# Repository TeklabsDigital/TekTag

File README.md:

# **TekTag Bio™ - The Open Source Biosensor**

Introducing the latest open-source project from Teklabs Digital™, a sophisticated state-of-the-art IoT biosensor for patient monitoring, telehealth, pressure are management in hospitals, cardiac monitoring, fall detection and dementia geofencing. This community project, released under an open source license, showcases our commitment to pushing the boundaries of digital design innovation.

**TekTag Bio™** is a cutting-edge biosensor for telehealth, patient monitoring, fall detection, dementia geofencing, and cardiograms. This repository houses all the necessary files and resources to understand, modify, and contribute to this innovative project.

## **Table of Contents**

- [Features](#features)
- [Biosensor Applications](#biosensor-applications)
- [General Applications](#general-applications)
- [BLE Support and Mesh Technology](#ble-support-and-mesh-technology)
  - [Benefits of BLE Mesh Technology](#benefits-of-ble-mesh-technology)
- [Hardware/Electronics](#hardwareelectronics)
- [Repository Structure](#repository-structure)
- [Images](#images)
- [PCB Size and Assembly](#pcb-size-and-assembly)
- [Why is this project Open Source?](#why-is-this-project-open-source)
- [Supporting This Project](#supporting-this-project)
- [Licenses](#licenses)
- [Contact Us](#contact-us)

## [**Features**](#features)
- Small size - 28mm diameter (1.1 inches)
- All 3D manufacturing files included
- All PCB designs included
- All schematics included
- Audio feedback
- BLE 5.4 - Mesh Networking & All protocols supported by the STM32WB
- Compact integrated design
- Haptic feedback
- Qi charging
- STM32WB ARM MCU
- Touch pad for finger tap and gestures
- Ultra low power
- Visual feedback through two RGB LEDs

## [Biosensor Applications](#biosensor-applications)

Our biosensor provides a plethora of features designed to enhance the quality of life for individuals and improve the capabilities of healthcare providers. It includes:

- Telehealth capabilities
- Patient monitoring
- Pressure area management - bed turn and movement detection
- Cardiac monitoring via Ballistocardiology (BCG)
- Patient Fall detection
- Dementia geo-fence alerting
- Respiratory monitoring
- Sleep pattern monitoring

## [General Applications](#general-applications)

The small size, wireless Bluetooth, hermetically sealed enclosure, and Qi charging features of the sensor make it versatile enough to be used in a wide variety of applications, such as:

- Sports Performance Analysis
- Physical Therapy
- Elderly Care
- Virtual Reality (VR)/ Augmented Reality (AR) Systems
- Gaming
- Industrial Monitoring
- Sleep Studies
- Dance Choreography
- Wildlife Studies
- Security Systems

## [BLE Support and Mesh Technology](#ble-support-and-mesh-technology)

One of the key features of the TekTag Bio™ is its compatibility with the STM32WB ecosystem, which offers support for a variety of Bluetooth Low Energy (BLE) protocols. BLE is a power-efficient version of classic Bluetooth and is designed for short-range communication between devices. 

A particularly exciting protocol within this ecosystem is BLE Mesh technology. BLE Mesh allows for many-to-many communication, creating a network of interconnected devices that can communicate with each other. This is an essential feature when deploying large numbers of TekTag Bio™ devices in a hospital setting.

### [Benefits of BLE Mesh Technology](#benefits-of-ble-mesh-technology)

There are several key benefits of using BLE Mesh technology in a TekTag Bio™ deployment:

1. **Scalability**: BLE Mesh networks can theoretically support up to 32,767 devices, making them highly scalable. This is ideal for large-scale deployments in hospitals, where you might need to monitor many patients simultaneously.
2. **Reliability**: In a mesh network, data can take multiple paths to reach its destination, which increases the network's overall reliability. If one device fails or is disconnected, the network can automatically reconfigure itself to ensure data still reaches its destination.
3. **Range**: While individual BLE devices have a limited range, a mesh network can extend that range significantly. Each device in the network can act as a relay, passing messages from one device to another. This allows data to travel large distances across the network, making it possible to cover an entire hospital.
4. **Power Efficiency**: Despite their capabilities, BLE Mesh networks are highly power efficient. This is crucial for TekTag Bio™ devices, which need to operate for extended periods without recharging.

## [Hardware/Electronics](#hardwareelectronics)

Our biosensor utilizes a range of high-performance components to achieve its functionality:

- **STM32WB55VG:** This is a BLE 5.3 dual-core, multi-protocol 2.4 GHz radio and ultra-low-power MCU system on chip. Supporting mesh networking, the STM32WB is the brain of our sensor and responsible for signal processing and wireless communication.

- **MLPF-WB55-01E3:** This is an integrated filter module for STM32WB55, by ST. It increases board space through reduced PCB component count.

- **BQ51052BYFP:** This is a high-efficiency, Qi-compliant wireless power receiver. It enables our sensor to be charged wirelessly.

- **TLV75533PDRV:** This is a low-dropout (LDO) regulator with high power-supply rejection ratio (PSRR). It helps to provide stable power supply for our sensor.

- **KTD2052:** This is an LED driver used for status indication in our sensor.

- **LSM6DSV16XTR:** This is a system-in-package featuring a 3D digital accelerometer and a 3D digital gyroscope. It enables our sensor to detect and log movements.

## [Repository Structure](#repository-structure)

This repository is organized into several key sections:

- **Electronics:** Schematics, PCB updates and files related to the electronic components of the TekTag Bio™ biosensor.
- **Firmware/stm32:** The initial commit of the firmware for the STM32 microcontroller used in the device.
- **Mechanical:** Files related to the mechanical aspects of the biosensor, including design and assembly instructions.

## [Images](#images)

Below are some images related to the project:

### PCB Front - 6 Layers
Having a six-layer PCB with tented vias under a BGA (Ball Grid Array) is important for our product's compact size, signal integrity, thermal management, and reliability. The extra layers allow for denser routing, reducing PCB size. Tented vias prevent solder draw into vias, preventing assembly problems under tight constraints.

### PCB Front 3D

### PCB Back 3D

### TekTag Bio™ Sensor with Silicon Holder

### TekTag Bio™ Sensor Without Silicone Holder

## [PCB Size and Assembly](#pcb-size-and-assembly)

The TekTag Bio™ is designed with a compact and highly-integrated PCB (Printed Circuit Board). Given its small size, specialized tools and expertise are required for the assembly process. This could pose a challenge for individual builders, especially those without access to such resources.

Understanding this, if there is enough interest from the community, we are prepared to step in and help. We plan to manufacture and assemble the boards for everyone at minimal cost. This not only ensures the quality and consistency of the boards but also makes the TekTag Bio™ more accessible to everyone interested in using or contributing to it.

## [Why is this project Open Source?](#why-is-this-project-open-source)

TekTag Bio™ is a project rooted in the belief that quality healthcare should be accessible to everyone, regardless of where they are in the world. By open sourcing this project, we are aiming to democratize access to technology that has the potential to significantly improve patient outcomes, particularly in developing countries where resources may be limited. 

There are several reasons why we believe an open source approach is best for this project:

1. **Community Collaboration**: Open source projects foster a unique sense of collaboration and community. People from all around the world can contribute to the project, each bringing their unique perspectives and skills to the table. This diversity can drive innovation and improve the product in ways that wouldn't be possible in a closed source project.

2. **Accelerated Development**: With more eyes on the project, issues can be identified and resolved more quickly. This can speed up the development process and result in a better final product.

3. **Transparency**: Open source projects are transparent. Anyone can look at the code and understand exactly how the product works. This transparency can build trust and make it easier for people to adopt the technology.

4. **Accessibility**: Perhaps the most important reason is that open source projects are accessible to everyone. Anyone, anywhere, can use and modify the product for their own needs. This is particularly important for healthcare technology, which has the potential to save lives and improve quality of life for millions of people.

5. **Non-profit Motivation**: As a non-profit initiative, our primary goal is to support health outcomes worldwide. Our focus is on creating a product that can have a real impact on the world, not on generating profit.

6. **Education**: Open sourcing this project also provides a valuable learning resource for students and professionals interested in biosensor technology. They can learn from and build upon the work that's already been done, accelerating their own learning and development.

By open sourcing TekTag Bio™, we hope to create a product that's not only effective, but also widely accessible and continually improving. This is our contribution to supporting healthcare in both developing countries and in first world hospitals where critical care is needed. We invite you to join us in this endeavor, whether it's by using TekTag Bio™, contributing to its development, or simply learning from the project.

## [Supporting This Project](#supporting-this-project)

TekTag Bio™ is a community-driven project, and we welcome contributions from everyone, regardless of their background or experience level. There are several ways you can support this project:

1. **Contributing Code**: If you have experience in UX/UI for the web application, Node.js for backend development, Express.js for the frontend, or STM32WB firmware engineering, your skills are particularly valuable. You can contribute directly to the codebase, helping us improve and expand the functionality of TekTag Bio™.

2. **Testing and Reporting Issues**: Even if you're not a developer, you can still contribute by testing the TekTag Bio™ and reporting any issues or bugs you find. This helps us ensure that the TekTag Bio™ is as reliable and effective as possible.

3. **Spreading the Word**: Help us grow the TekTag Bio™ community by sharing the project with others. The more people who know about TekTag Bio™, the more we can achieve.

4. **Donations**: As a not-for-profit project, we rely on donations to fund our work. If you're able to, consider making a donation to support the development of TekTag Bio™.

5. **Partnerships**: We are open to partnerships with organizations that align with our mission of improving healthcare outcomes worldwide. If you represent such an organization, please get in touch.

## [Licenses](#licenses)
Project source code, hardware designs and 3d enclosure designs are open source and licensed under the terms of the attached license, with attribution to TekLabs Digital Pty Ltd, Australia

## [Contact Us](#contact-us)
If you're interested in contributing to the TekTag Bio™ project, please contact us through our website at [https://teklabsdigital.com/contact/](https://teklabsdigital.com/contact/). We look forward to working with you to make TekTag Bio™ the best it can be!

Remember, every contribution, no matter how small, helps us move closer to our goal of improving healthcare outcomes around the world. Thank you for your support!

About TekLabs Digital Pty Ltd, Australia - Creating exceptional IoT products and advanced technologies to improve our quality of life 🌟IoT product research, innovation and design✨Let's get started!
web www.teklabsdigital.com
linkedin https://www.linkedin.com/in/trevorattemadigital/
Contact us about your design today.

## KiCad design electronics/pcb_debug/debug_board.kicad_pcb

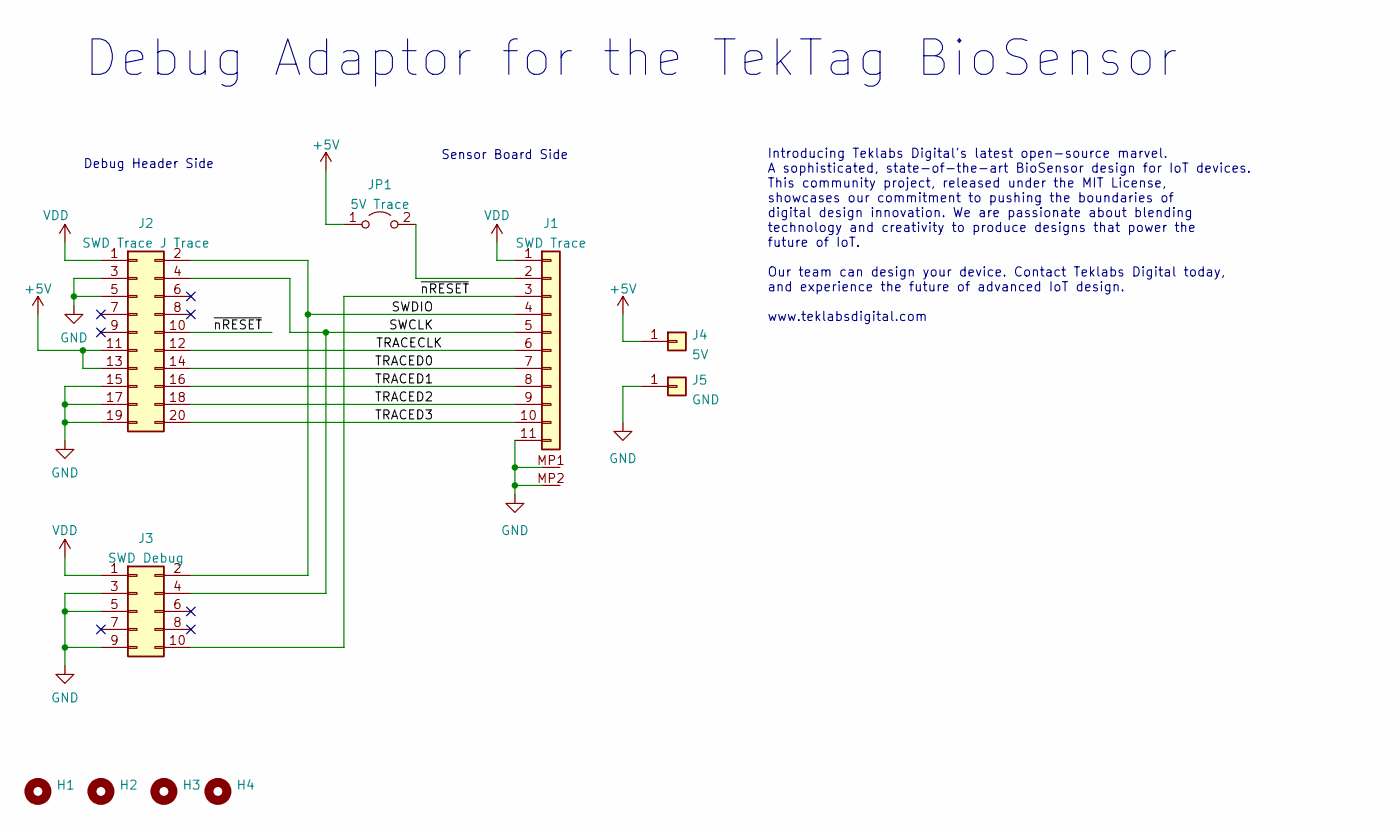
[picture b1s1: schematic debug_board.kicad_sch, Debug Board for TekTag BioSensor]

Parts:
H1, H2, H3, H4: MountingHole; MountingHole_3.7mm_Pad_TopBottom
J1: SWD Trace; Molex 5035661102; Digikey 900-5035661102CT-ND
J2: SWD Trace J Trace; PinHeader_2x10_P1.27mm_Vertical; Digikey 2057-HPH2-A-20-UA-ND
J3: SWD Debug; PinHeader_2x05_P1.27mm_Vertical
J4: 5V; PinHeader_1x01_P2.54mm_Vertical
J5: GND; PinHeader_1x01_P2.54mm_Vertical
JP1: 5V Trace; PinHeader_1x02_P2.54mm_Vertical

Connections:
+5V: J2.11, J2.13, J4.1, JP1.1 (A)
/SWCLK: J1.5, J2.4, J3.4
/SWDIO: J1.4, J2.2, J3.2
/TRACECLK: J1.6, J2.12
/TRACED0: J1.7, J2.14
/TRACED1: J1.8, J2.16
/TRACED2: J1.9, J2.18
/TRACED3: J1.10, J2.20
/~nRESET: J1.3, J2.10, J3.10
GND: J1.11, J1.MP1, J1.MP2, J2.3, J2.5, J2.15, J2.17, J2.19, J3.3, J3.5, J3.9, J5.1
unnamed: J1.2, JP1.2 (B)
VDD: J1.1, J2.1, J3.1

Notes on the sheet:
Sensor Board Side
Debug Adaptor for the TekTag BioSensor
Debug Header Side
Introducing Teklabs Digital's latest open-source marvel. A sophisticated, state-of-the-art BioSensor design for IoT devices. This community project, released under the MIT License, showcases our commitment to pushing the boundaries of digital design innovation. We are passionate about blending tech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

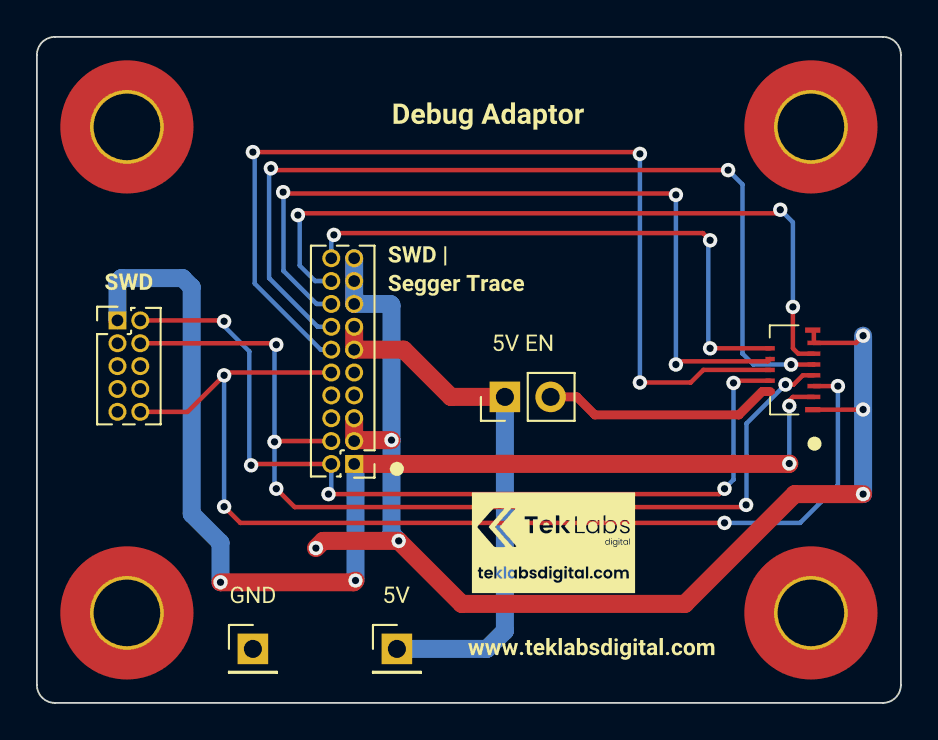
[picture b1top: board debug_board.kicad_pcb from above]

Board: 2 copper layers, 48.0 x 37.0 mm, 17 parts (0 on the bottom side), 12 nets.

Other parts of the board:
kibuzzard-64C06F13: G***; kibuzzard-64C06F13
kibuzzard-64C06F53: G***; kibuzzard-64C06F53
kibuzzard-64C082C5: G***; kibuzzard-64C082C5
kibuzzard-64C0828D: G***; kibuzzard-64C0828D
kibuzzard-64C06064: G***; kibuzzard-64C06064
kibuzzard-64C08352: G***; kibuzzard-64C08352
kibuzzard-64757A2A: G***; kibuzzard-64757A2A

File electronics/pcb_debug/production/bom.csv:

Designator,Footprint,Quantity,Value,LCSC Part #
J1,Molex 5035661102,1,SWD Trace,
J2,PinHeader_2x10_P1.27mm_Vertical,1,SWD Trace J Trace,
J3,PinHeader_2x05_P1.27mm_Vertical,1,SWD Debug,
J4,PinHeader_1x01_P2.54mm_Vertical,1,5V,
J5,PinHeader_1x01_P2.54mm_Vertical,1,GND,
JP1,PinHeader_1x02_P2.54mm_Vertical,1,5V Trace,

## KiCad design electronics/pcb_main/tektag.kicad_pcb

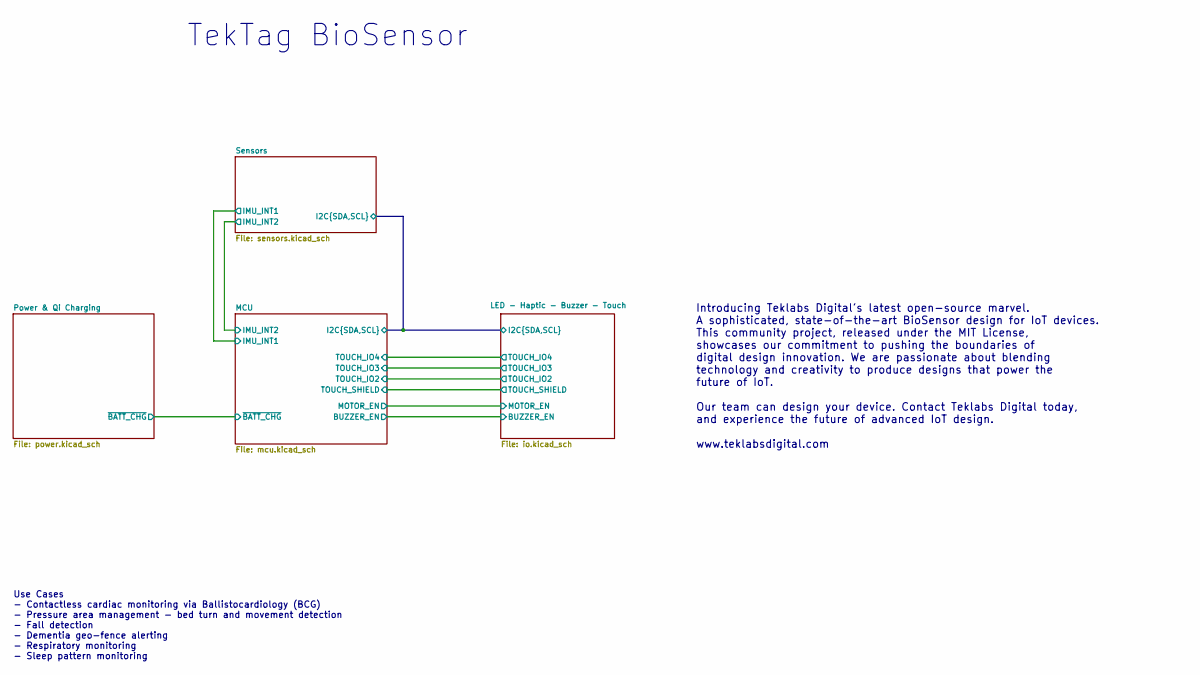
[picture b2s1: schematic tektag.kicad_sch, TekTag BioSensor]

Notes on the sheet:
Introducing Teklabs Digital's latest open-source marvel. A sophisticated, state-of-the-art BioSensor design for IoT devices. This community project, released under the MIT License, showcases our commitment to pushing the boundaries of digital design innovation. We are passionate about blending tech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
Use Cases - Contactless cardiac monitoring via Ballistocardiology (BCG) - Pressure area management - bed turn and movement detection - Fall detection - Dementia geo-fence alerting - Respiratory monitoring - Sleep pattern monitoring
TekTag BioSensor

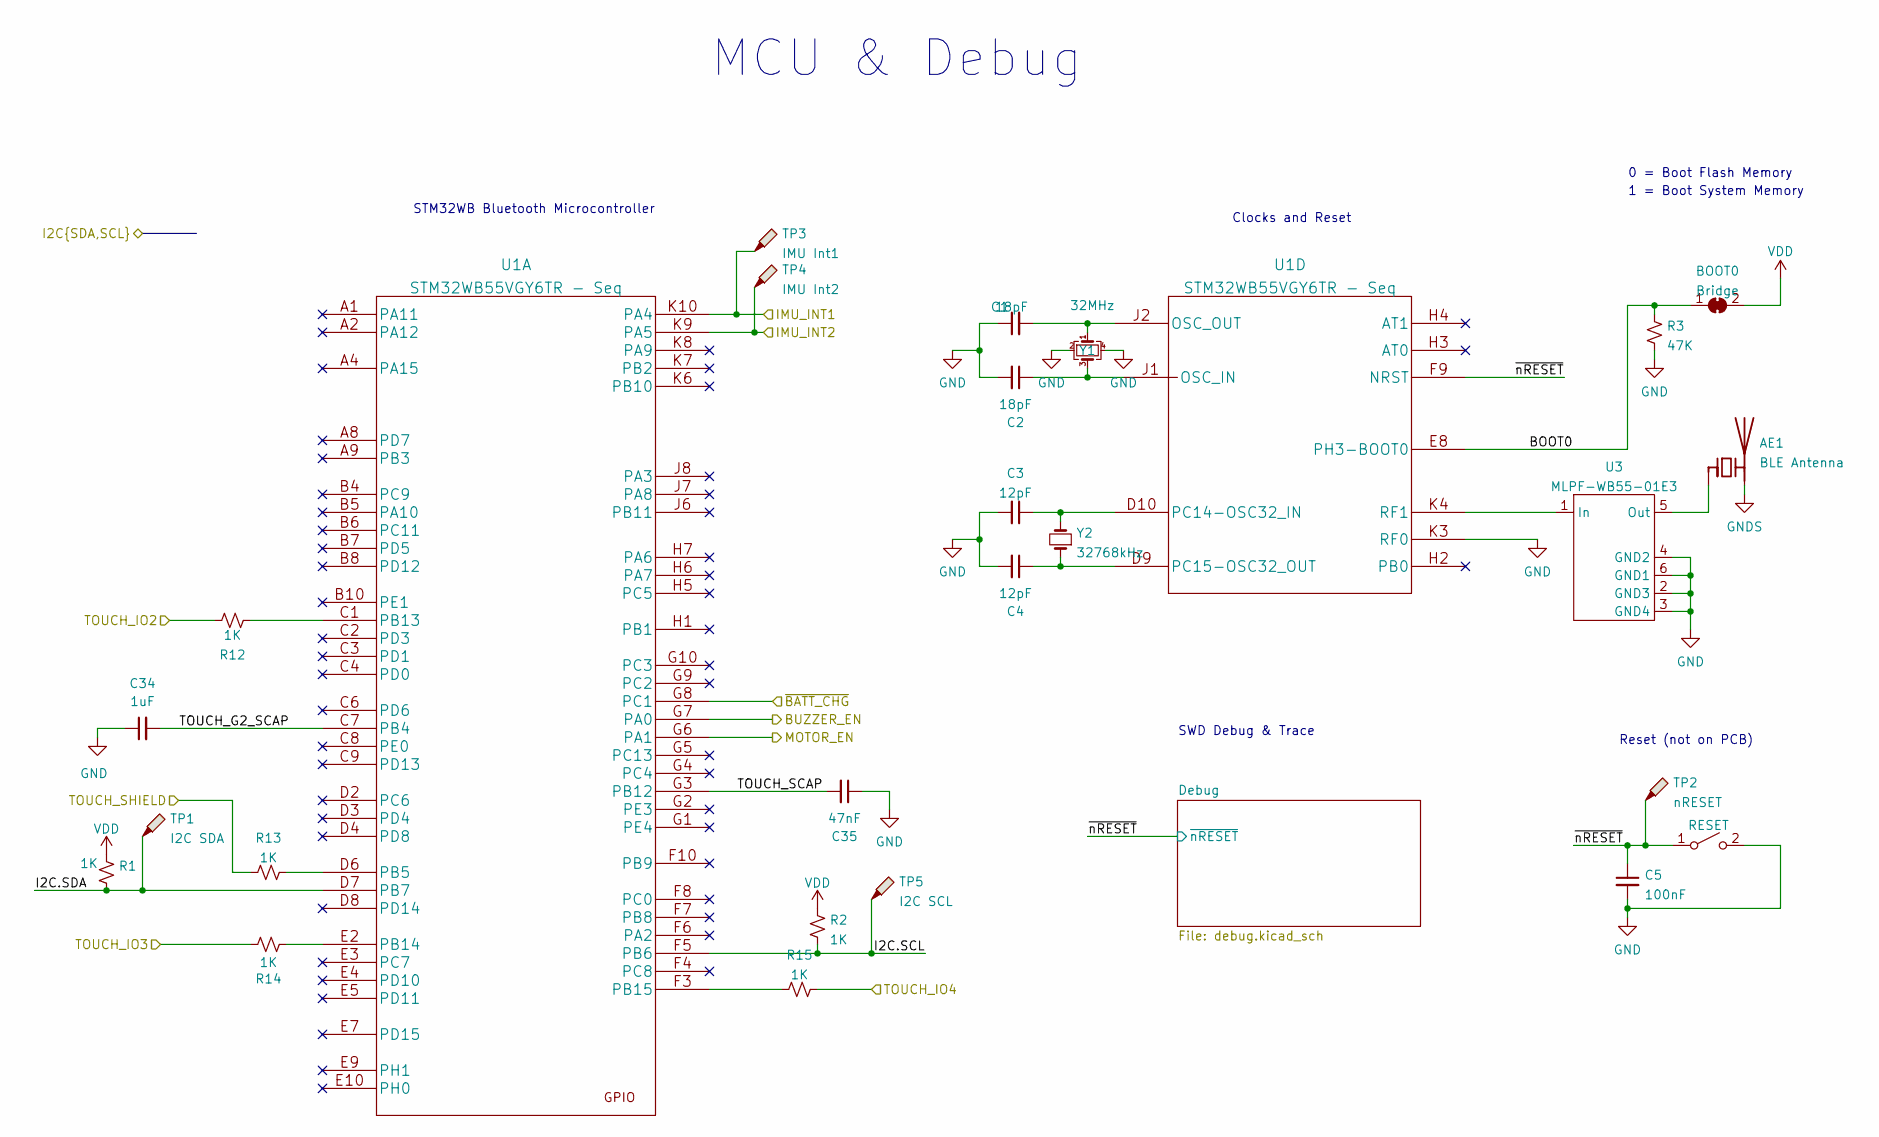
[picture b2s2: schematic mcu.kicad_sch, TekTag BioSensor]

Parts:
AE1: BLE Antenna
BOOT0: Bridge
C1, C2: 18pF; Digikey GCM1555C1H180JA16D
C3, C4: 12pF; Digikey GCM1555C1H120JA16J
C5: 100nF; Digikey GRT155R71H104KE01D
C34: 1uF; Digikey EMK105BJ105KV-F
C35: 47nF; Digikey GRM155R71H473ME14D
R1, R2, R12, R13, R14, R15: 1K; Digikey 1292-WR04X1001FTLCT-ND
R3: 47K; Digikey 311-47.0KLRCT-ND
SW1: RESET; Digikey B3U-1100P
TP1: I2C SDA
TP2: nRESET
TP3: IMU Int1
TP4: IMU Int2
TP5: I2C SCL
U1: STM32WB55VGY6TR - Seq
U3: MLPF-WB55-01E3; Digikey 497-19088-2-ND
Y1: 32MHz; Digikey 1923-830107820709CT-ND
Y2: 32768kHz; Digikey 2195-CM9V-T1A-32.768KHZ-7PF-100PPM-TA-Q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

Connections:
/LED - Haptic - Buzzer - Touch/BUZZER_EN: U1.G7 (PA0); also elsewhere on the board
/LED - Haptic - Buzzer - Touch/I2C.SCL: R2.2, TP5.1, U1.F5 (PB6); also elsewhere on the board
/LED - Haptic - Buzzer - Touch/I2C.SDA: R1.2, TP1.1, U1.D7 (PB7); also elsewhere on the board
/LED - Haptic - Buzzer - Touch/MOTOR_EN: U1.G6 (PA1); also elsewhere on the board
/LED - Haptic - Buzzer - Touch/TOUCH_IO2: R12.2; also elsewhere on the board
/LED - Haptic - Buzzer - Touch/TOUCH_IO3: R14.2; also elsewhere on the board
/LED - Haptic - Buzzer - Touch/TOUCH_IO4: R15.2; also elsewhere on the board
/LED - Haptic - Buzzer - Touch/TOUCH_SHIELD: R13.2; also elsewhere on the board
/MCU/BOOT0: BOOT0.1 (A), R3.1, U1.E8 (PH3-BOOT0)
/MCU/IMU_INT1: TP3.1, U1.K10 (PA4); also elsewhere on the board
/MCU/IMU_INT2: TP4.1, U1.K9 (PA5); also elsewhere on the board
/MCU/TOUCH_G2_SCAP: C34.2, U1.C7 (PB4)
/MCU/TOUCH_SCAP: C35.2, U1.G3 (PB12)
/MCU/~BATT_CHG: U1.G8 (PC1); also elsewhere on the board
/MCU/~nRESET: C5.1, SW1.1 (A), TP2.1, U1.F9 (NRST); also elsewhere on the board
GND: C1.1, C2.2, C3.2, C4.2, C5.2, C34.1, C35.1, R3.2, SW1.2 (B), U1.K3 (RF0), U3.2 (GND3), U3.3 (GND4), U3.4 (GND2), U3.6 (GND1), Y1.2, Y1.4; also elsewhere on the board
GNDS: AE1.2 (PCB_Trace)
unnamed: AE1.1 (FEED), U3.5 (Out)
unnamed: C1.2, U1.J2 (OSC_OUT), Y1.1
unnamed: C2.1, U1.J1 (OSC_IN), Y1.3
unnamed: C3.1, U1.D10 (PC14-OSC32_IN), Y2.2
unnamed: C4.1, U1.D9 (PC15-OSC32_OUT), Y2.1
unnamed: R12.1, U1.C1 (PB13)
unnamed: R13.1, U1.D6 (PB5)
unnamed: R14.1, U1.E2 (PB14)
unnamed: R15.1, U1.F3 (PB15)
unnamed: U1.K4 (RF1), U3.1 (In)
VDD: BOOT0.2 (B), R1.1, R2.1; also elsewhere on the board

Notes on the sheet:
0 = Boot Flash Memory
1 = Boot System Memory
Reset (not on PCB)
MCU & Debug
SWD Debug & Trace
Clocks and Reset
STM32WB Bluetooth Microcontroller

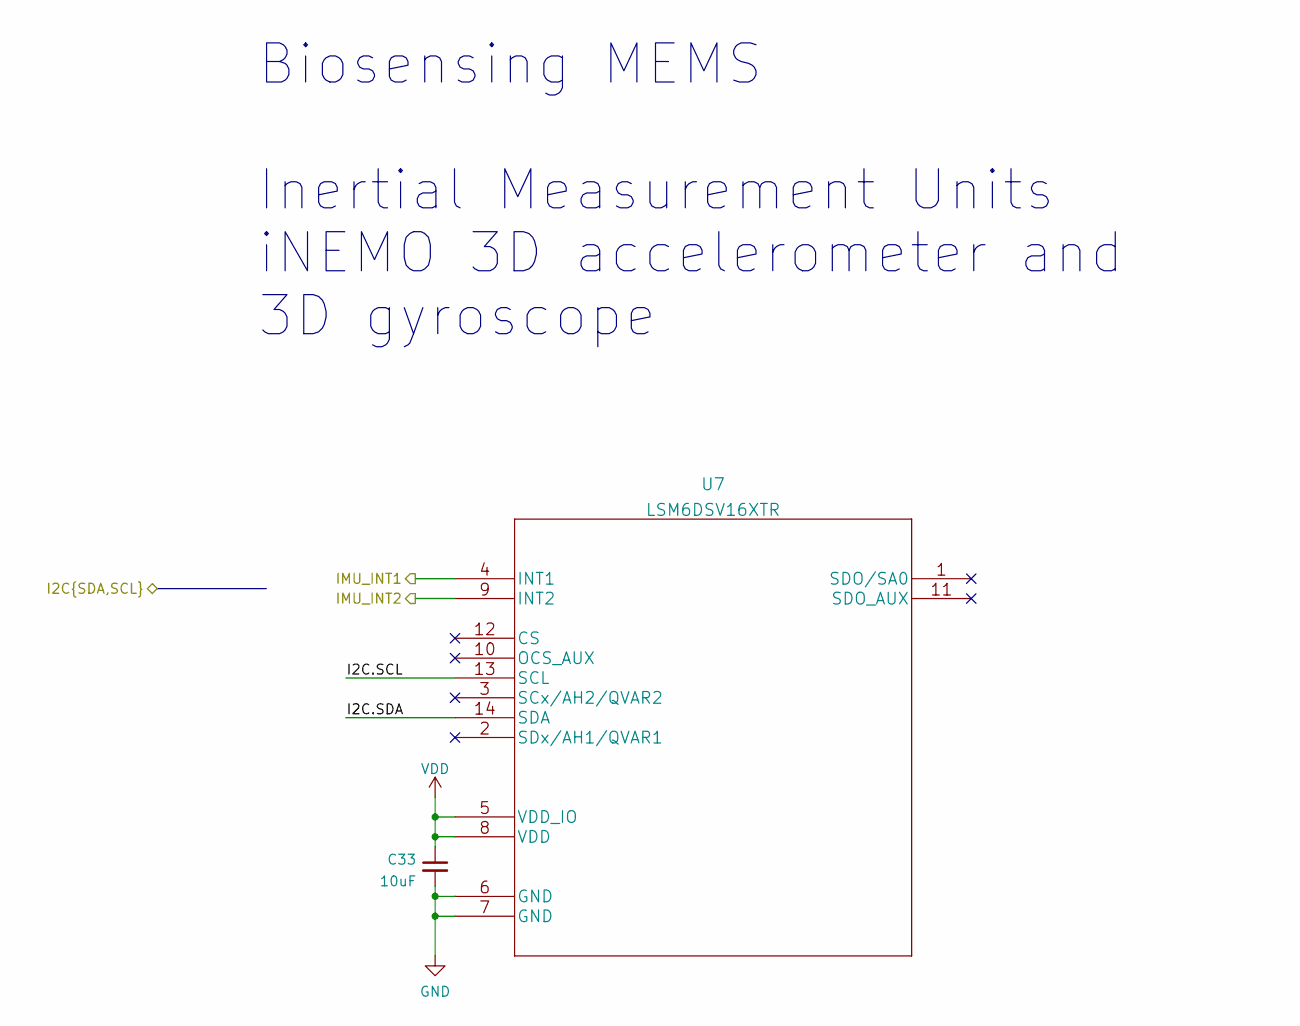
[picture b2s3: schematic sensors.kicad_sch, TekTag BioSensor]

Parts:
C33: 10uF; Digikey GRM188R6YA106MA73D
U7: LSM6DSV16XTR

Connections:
/LED - Haptic - Buzzer - Touch/I2C.SCL: U7.13 (SCL); also elsewhere on the board
/LED - Haptic - Buzzer - Touch/I2C.SDA: U7.14 (SDA); also elsewhere on the board
/MCU/IMU_INT1: U7.4 (INT1); also elsewhere on the board
/MCU/IMU_INT2: U7.9 (INT2); also elsewhere on the board
GND: C33.2, U7.6 (GND), U7.7 (GND); also elsewhere on the board
VDD: C33.1, U7.5 (VDD_IO), U7.8 (VDD); also elsewhere on the board

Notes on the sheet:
Biosensing MEMS Inertial Measurement Units iNEMO 3D accelerometer and 3D gyroscope

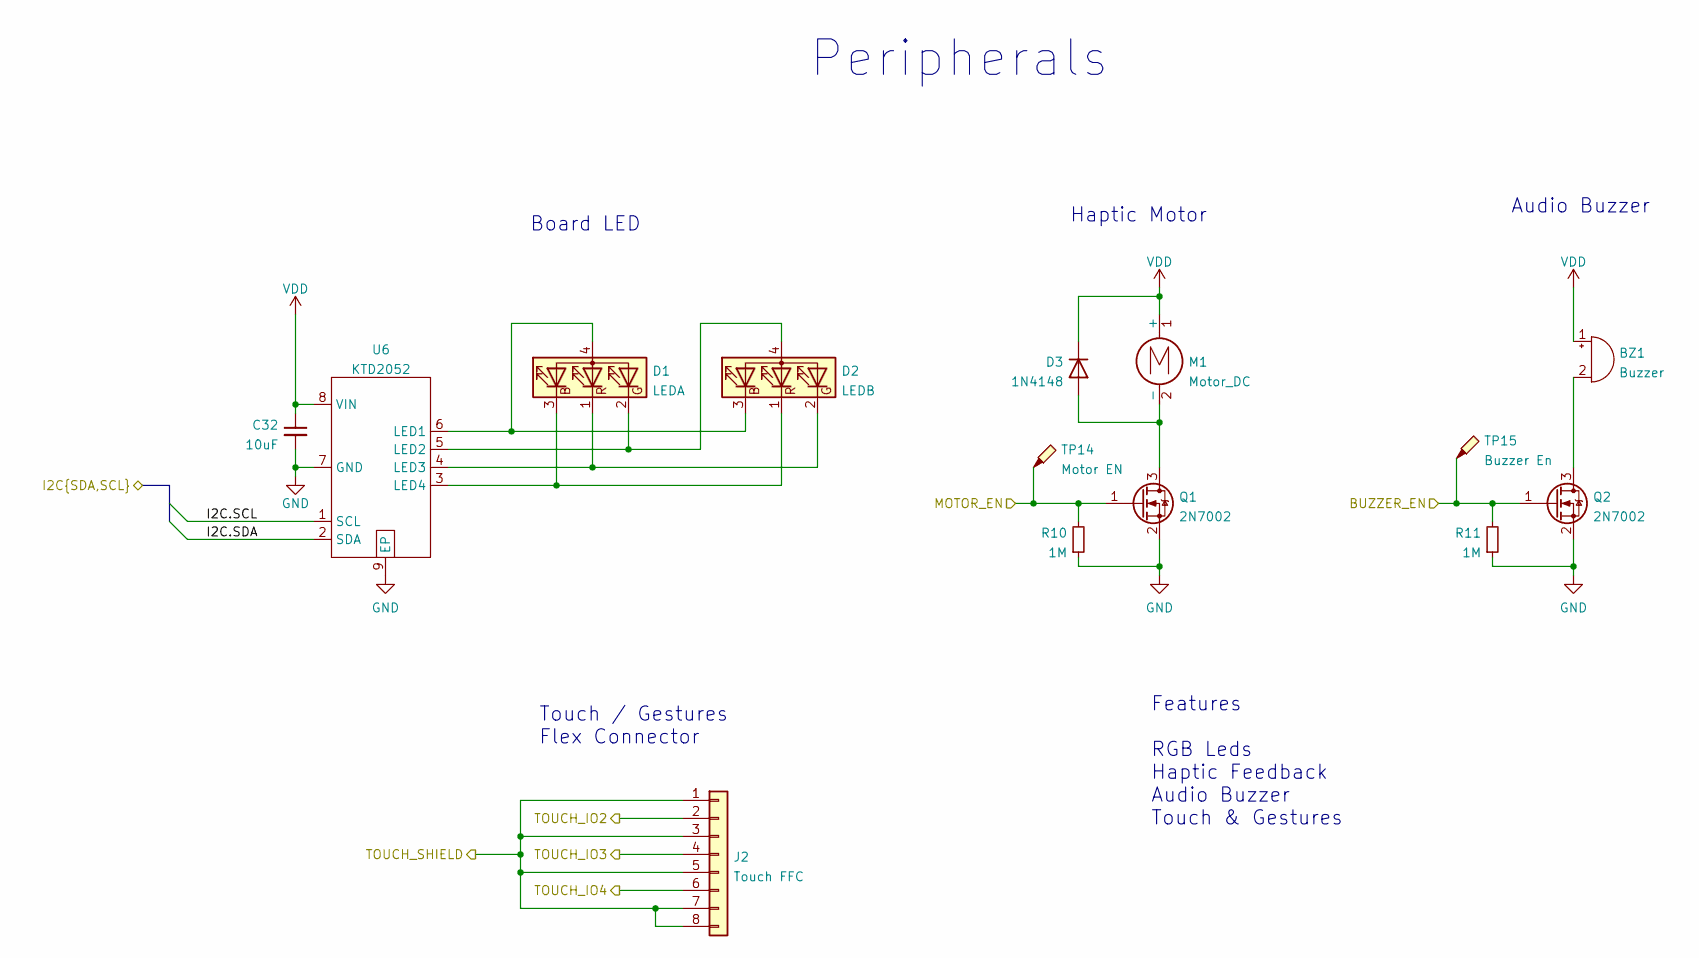
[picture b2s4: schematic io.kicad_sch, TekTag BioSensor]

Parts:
BZ1: Buzzer
C32: 10uF; Digikey GRM188R6YA106MA73D
D1: LEDA; Digikey LTST-C19HE1WT
D2: LEDB; Digikey LTST-C19HE1WT
D3: 1N4148; Digikey 1N4148WL2-TP
J2: Touch FFC
M1: Motor_DC; Digikey 1670-VZ43FM1B8230001LCT-ND
Q1, Q2: 2N7002; Digikey 2N7002KL3A-TP
R10, R11: 1M; Digikey 311-1.00MLRCT-ND
TP14: Motor EN
TP15: Buzzer En
U6: KTD2052

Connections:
/LED - Haptic - Buzzer - Touch/BUZZER_EN: Q2.1 (G), R11.2, TP15.1; also elsewhere on the board
/LED - Haptic - Buzzer - Touch/I2C.SCL: U6.1 (SCL); also elsewhere on the board
/LED - Haptic - Buzzer - Touch/I2C.SDA: U6.2 (SDA); also elsewhere on the board
/LED - Haptic - Buzzer - Touch/MOTOR_EN: Q1.1 (G), R10.2, TP14.1; also elsewhere on the board
/LED - Haptic - Buzzer - Touch/TOUCH_IO2: J2.2; also elsewhere on the board
/LED - Haptic - Buzzer - Touch/TOUCH_IO3: J2.4; also elsewhere on the board
/LED - Haptic - Buzzer - Touch/TOUCH_IO4: J2.6; also elsewhere on the board
/LED - Haptic - Buzzer - Touch/TOUCH_SHIELD: J2.1, J2.3, J2.5, J2.7, J2.8; also elsewhere on the board
GND: C32.2, Q1.2 (S), Q2.2 (S), R10.1, R11.1, U6.7 (GND), U6.9 (EP); also elsewhere on the board
unnamed: BZ1.2 (+), Q2.3 (D)
unnamed: D1.1 (RK), D2.2 (GK), U6.4 (LED3)
unnamed: D1.2 (GK), D2.4 (A), U6.5 (LED2)
unnamed: D1.3 (BK), D2.1 (RK), U6.3 (LED4)
unnamed: D1.4 (A), D2.3 (BK), U6.6 (LED1)
unnamed: D3.2 (A), M1.2 (-), Q1.3 (D)
VDD: BZ1.1 (-), C32.1, D3.1 (K), M1.1 (+), U6.8 (VIN); also elsewhere on the board

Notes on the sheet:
Peripherals
Haptic Motor
Audio Buzzer
Touch / Gestures Flex Connector
Board LED
Features RGB Leds Haptic Feedback Audio Buzzer Touch & Gestures

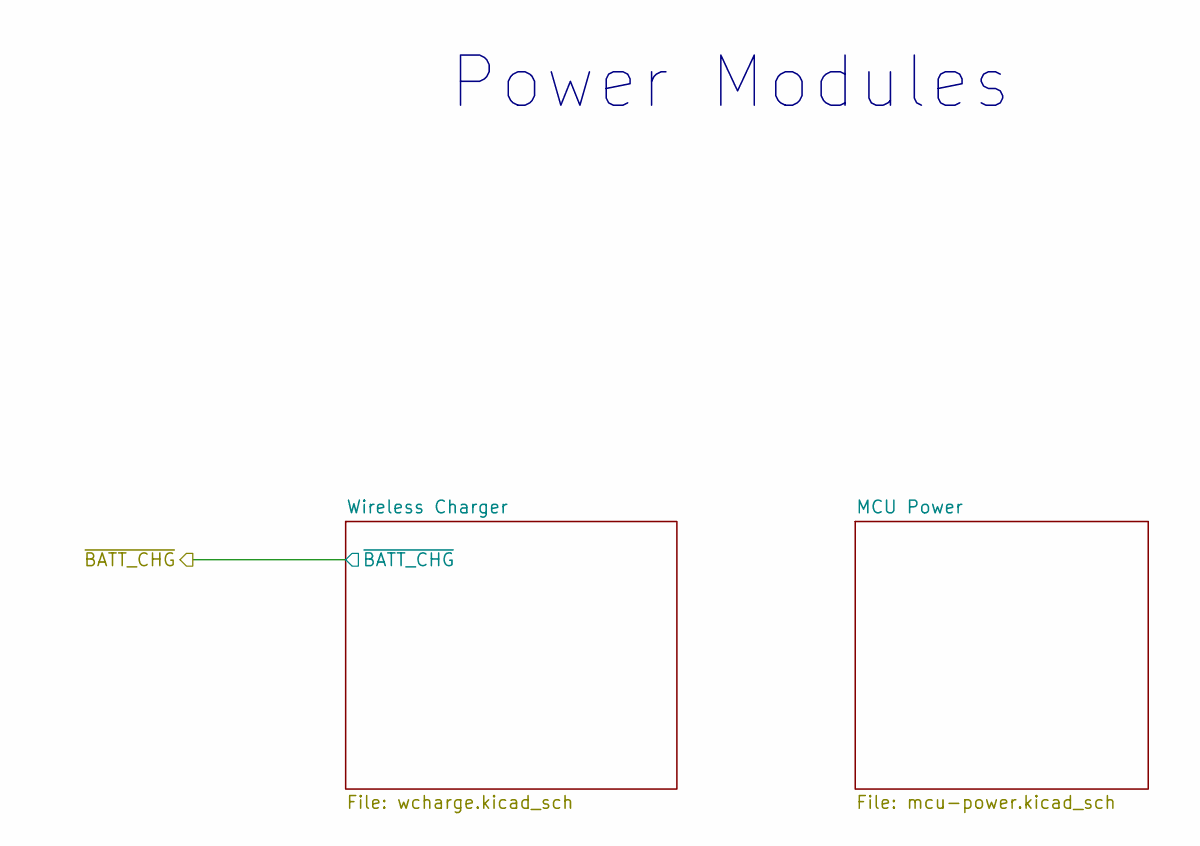
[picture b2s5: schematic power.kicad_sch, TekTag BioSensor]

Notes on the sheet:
Power Modules

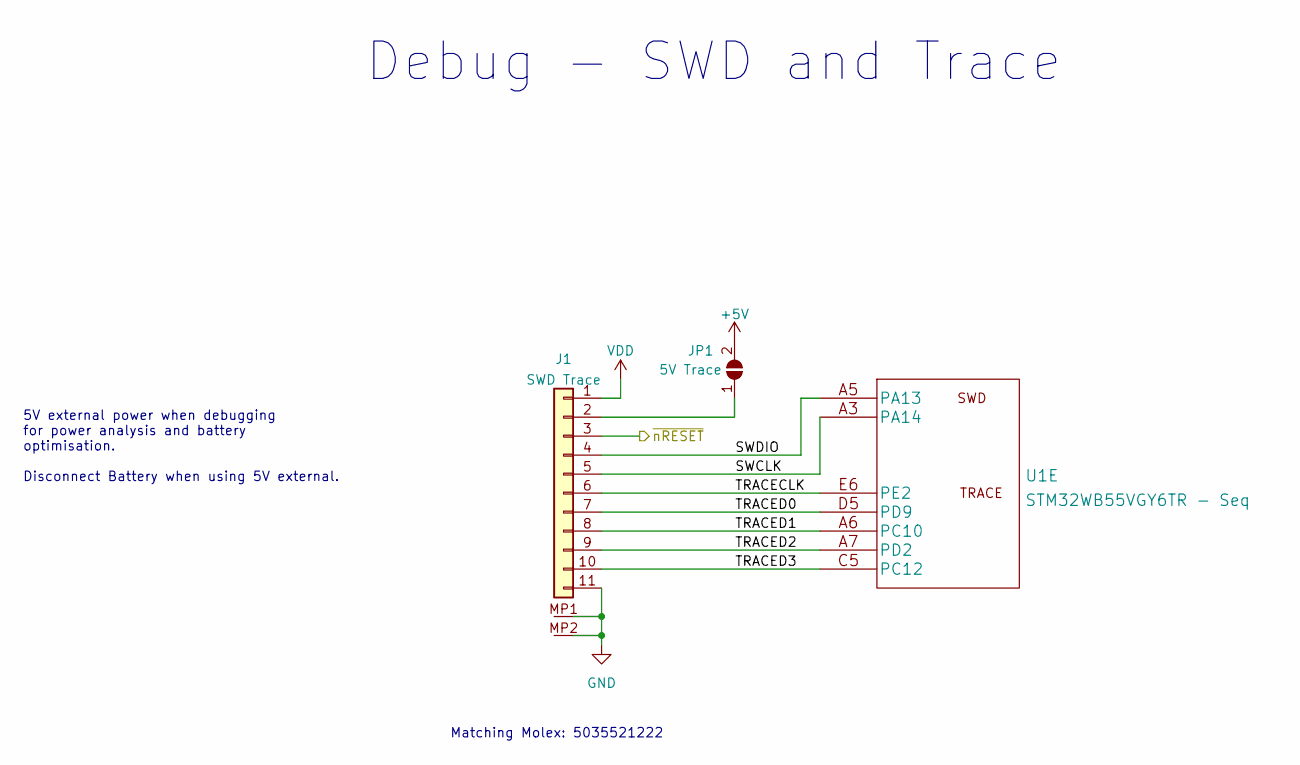
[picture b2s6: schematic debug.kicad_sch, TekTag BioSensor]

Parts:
J1: SWD Trace
JP1: 5V Trace
U1: STM32WB55VGY6TR - Seq

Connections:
+5V: JP1.2 (B); also elsewhere on the board
/MCU/Debug/SWCLK: J1.5, U1.A3 (PA14)
/MCU/Debug/SWDIO: J1.4, U1.A5 (PA13)
/MCU/Debug/TRACECLK: J1.6, U1.E6 (PE2)
/MCU/Debug/TRACED0: J1.7, U1.D5 (PD9)
/MCU/Debug/TRACED1: J1.8, U1.A6 (PC10)
/MCU/Debug/TRACED2: J1.9, U1.A7 (PD2)
/MCU/Debug/TRACED3: J1.10, U1.C5 (PC12)
/MCU/~nRESET: J1.3; also elsewhere on the board
GND: J1.11, J1.MP1, J1.MP2; also elsewhere on the board
unnamed: J1.2, JP1.1 (A)
VDD: J1.1; also elsewhere on the board

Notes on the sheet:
5V external power when debugging for power analysis and battery optimisation. Disconnect Battery when using 5V external.
Debug - SWD and Trace
Matching Molex: 5035521222

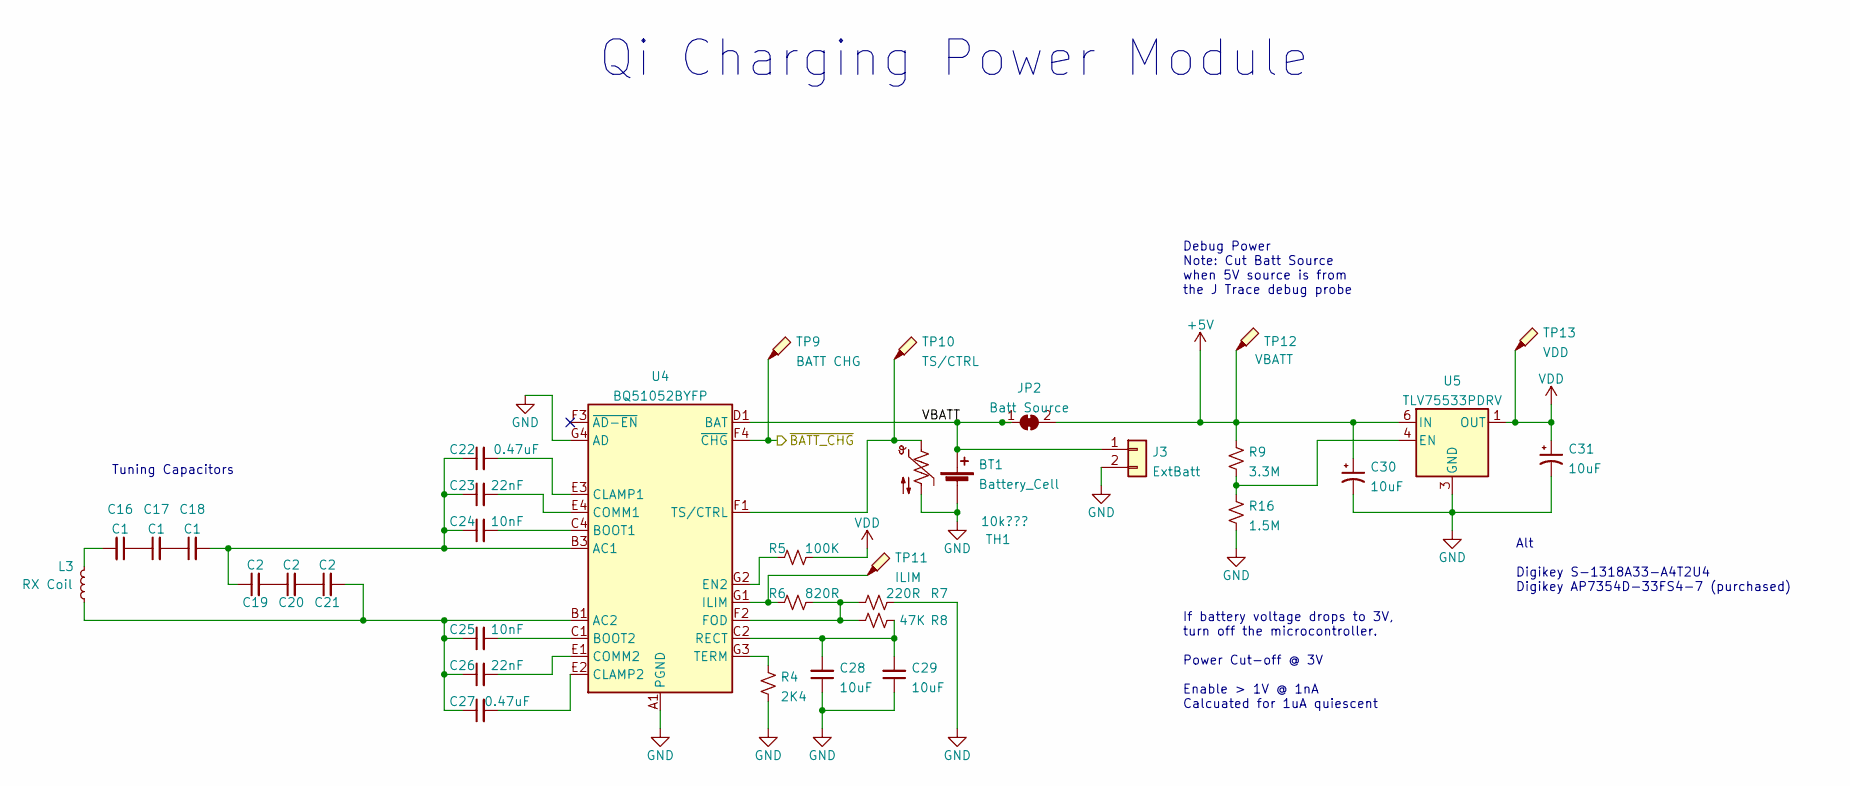
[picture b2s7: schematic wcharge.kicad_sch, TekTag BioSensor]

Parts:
BT1: Battery_Cell
C16, C17, C18: C1
C19, C20, C21: C2
C22, C27: 0.47uF; Digikey GRM155R71H473KE14J
C23, C26: 22nF; Digikey GRM155R71H223KA12D
C24, C25: 10nF; Digikey GCM155R71H103KA55J
C28, C29: 10uF
C30, C31: 10uF; Digikey GRM188R6YA106MA73D
J3: ExtBatt
JP2: Batt Source
L3: RX Coil
R4: 2K4; Digikey 311-2.40KLRCT-ND
R5: 100K; Digikey 311-100KLRCT-ND
R6: 820R; Digikey 311-820LRCT-ND
R7: 220R; Digikey 311-220LRCT-ND
R8: 47K; Digikey 311-47.0KLRCT-ND
R9: 3.3M; Digikey 311-3.30MLRCT-ND
R16: 1.5M; Digikey YAG5650CT-ND
TH1: 10k???
TP9: BATT CHG
TP10: TS/CTRL
TP11: ILIM
TP12: VBATT
TP13: VDD
U4: BQ51052BYFP
U5: TLV75533PDRV; Digikey 296-51807-2-ND

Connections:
+5V: C30.1, JP2.2 (B), R9.2, TP12.1, U5.6 (IN); also elsewhere on the board
/MCU/~BATT_CHG: TP9.1, U4.F4 (~CHG); also elsewhere on the board
/Power & Qi Charging/Wireless Charger/VBATT: BT1.1 (+), J3.1, JP2.1 (A), U4.D1 (BAT), U4.D2 (BAT), U4.D3 (BAT), U4.D4 (BAT)
GND: BT1.2 (-), C28.1, C29.1, C30.2, C31.2, J3.2, R4.1, R7.2, R16.1, TH1.2, U4.A1 (PGND), U4.A2 (PGND), U4.A3 (PGND), U4.A4 (PGND), U4.G4 (AD), U5.3 (GND), U5.7 (GND); also elsewhere on the board
unnamed: C16.1, C17.1
unnamed: C16.2, L3.2
unnamed: C17.2, C18.1
unnamed: C18.2, C19.1, C22.1, C23.1, C24.1, U4.B3 (AC1), U4.B4 (AC1)
unnamed: C19.2, C20.1
unnamed: C20.2, C21.1
unnamed: C21.2, C25.1, C26.1, C27.1, L3.1, U4.B1 (AC2), U4.B2 (AC2)
unnamed: C22.2, U4.E3 (CLAMP1)
unnamed: C23.2, U4.E4 (COMM1)
unnamed: C24.2, U4.C4 (BOOT1)
unnamed: C25.2, U4.C1 (BOOT2)
unnamed: C26.2, U4.E1 (COMM2)
unnamed: C27.2, U4.E2 (CLAMP2)
unnamed: C28.2, C29.2, R8.2, U4.C2 (RECT), U4.C3 (RECT)
unnamed: R4.2, U4.G3 (TERM)
unnamed: R5.1, U4.G2 (EN2)
unnamed: R6.1, TP11.1, U4.G1 (ILIM)
unnamed: R6.2, R7.1, R8.1, U4.F2 (FOD)
unnamed: R9.1, R16.2, U5.4 (EN)
unnamed: TH1.1, TP10.1, U4.F1 (TS/CTRL)
VDD: C31.1, R5.2, TP13.1, U5.1 (OUT); also elsewhere on the board

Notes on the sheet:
Debug Power Note: Cut Batt Source when 5V source is from the J Trace debug probe
Tuning Capacitors
Alt Digikey S-1318A33-A4T2U4 Digikey AP7354D-33FS4-7 (purchased)
If battery voltage drops to 3V, turn off the microcontroller. Power Cut-off @ 3V Enable > 1V @ 1nA Calcuated for 1uA quiescent
Qi Charging Power Module

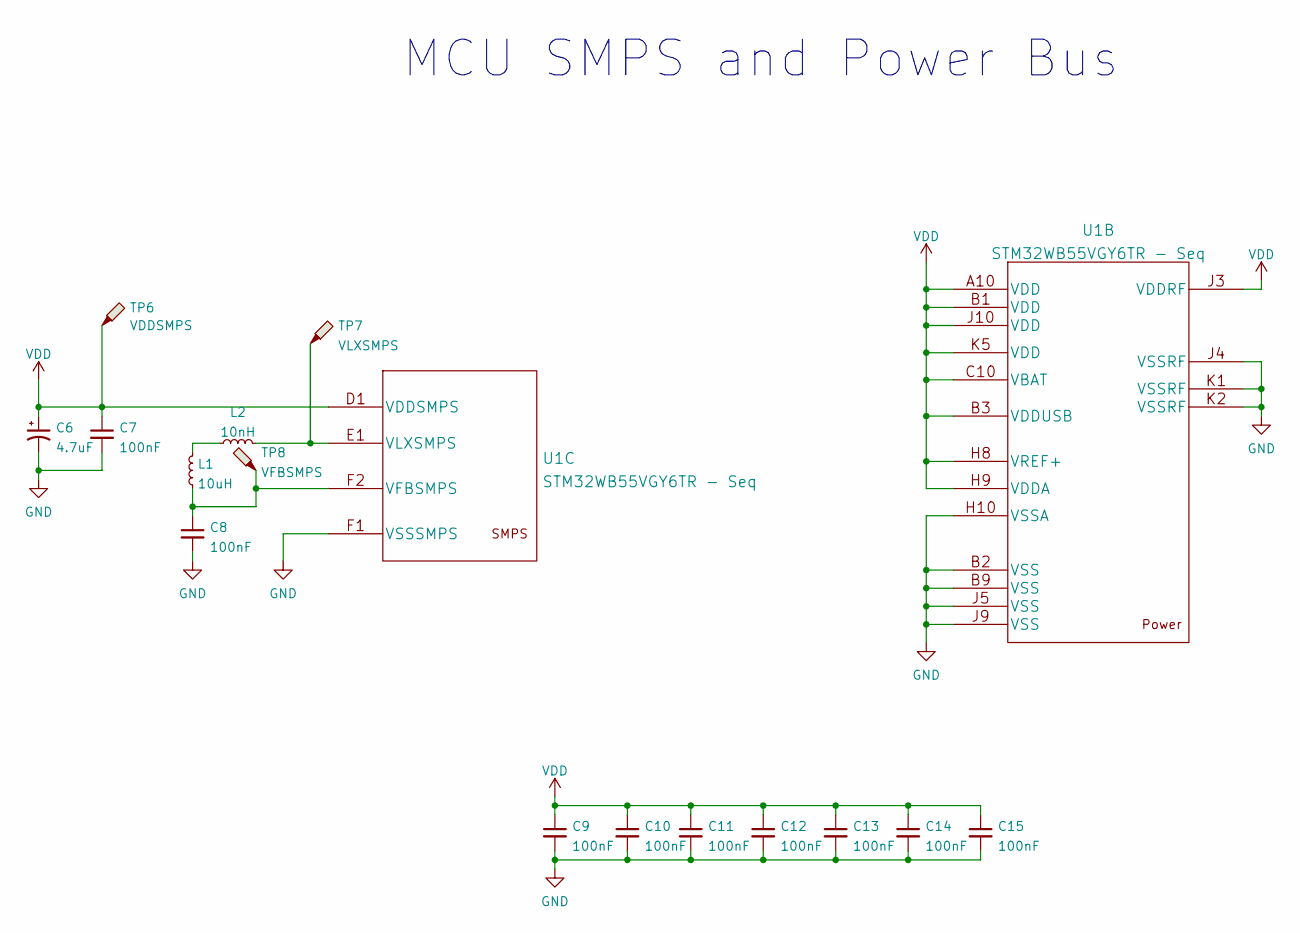
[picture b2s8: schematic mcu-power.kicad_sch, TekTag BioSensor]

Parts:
C6: 4.7uF; Digikey F981C475MMA
C7, C8, C9, C10, C11, C12, C13, C14, C15: 100nF; Digikey GRT155R71H104KE01D
L1: 10uH; Digikey MLZ1608N100LTD25
L2: 10nH; Digikey 7447860110G
TP6: VDDSMPS
TP7: VLXSMPS
TP8: VFBSMPS
U1: STM32WB55VGY6TR - Seq

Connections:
GND: C6.2, C7.2, C8.2, C9.2, C10.2, C11.2, C12.2, C13.2, C14.2, C15.2, U1.B2 (VSS), U1.B9 (VSS), U1.F1 (VSSSMPS), U1.H10 (VSSA), U1.J4 (VSSRF), U1.J5 (VSS), U1.J9 (VSS), U1.K1 (VSSRF), U1.K2 (VSSRF); also elsewhere on the board
unnamed: C8.1, L1.1, TP8.1, U1.F2 (VFBSMPS)
unnamed: L1.2, L2.1
unnamed: L2.2, TP7.1, U1.E1 (VLXSMPS)
VDD: C6.1, C7.1, C9.1, C10.1, C11.1, C12.1, C13.1, C14.1, C15.1, TP6.1, U1.A10 (VDD), U1.B1 (VDD), U1.B3 (VDDUSB), U1.C10 (VBAT), U1.D1 (VDDSMPS), U1.H8 (VREF+), U1.H9 (VDDA), U1.J3 (VDDRF), U1.J10 (VDD), U1.K5 (VDD); also elsewhere on the board

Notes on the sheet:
MCU SMPS and Power Bus

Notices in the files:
electronics/hardware/debug.kicad_sch:
© 2023 TekLabs Digital Pty Ltd
parts and their libraries:
Copyright 2021 Accelerated Designs. All rights reserved.
